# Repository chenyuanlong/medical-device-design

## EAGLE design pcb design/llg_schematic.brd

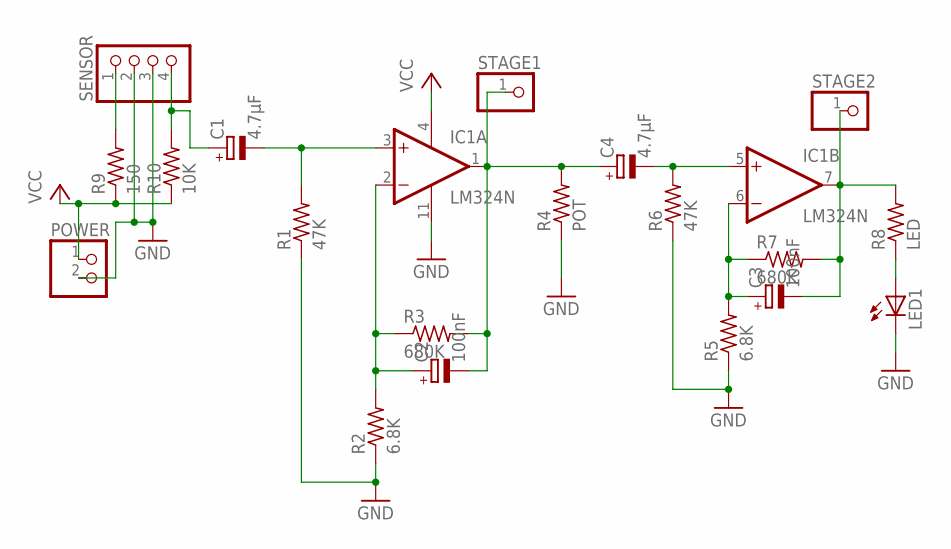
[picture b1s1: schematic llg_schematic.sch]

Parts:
C1, C4: 4.7μF; E2,5-6
C2, C3: 100nF; E2,5-6
IC1: LM324N; DIL14
LED1: LED5MM
POWER: PINHD-1X2; 1X02
R1, R6: 47K; 0204/7
R2, R5: 6.8K; 0204/7
R3, R7: 680K; 0204/7
R4: POT; 0204/7
R8: LED; 0204/7
R9: 150; 0204/7
R10: 10K; 0204/7
SENSOR: PINHD-1X4; 1X04
STAGE1, STAGE2: PINHD-1X1; 1X01

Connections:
GND: IC1.11 (V-), LED1.K (C), POWER.2, R1.1, R2.1, R4.1, R5.1, R6.1, SENSOR.2, SENSOR.3
unnamed: C1.-, IC1.3 (+IN), R1.2
unnamed: C2.+, IC1.2 (-IN), R2.2, R3.1
unnamed: C2.-, C4.+, IC1.1 (OUT), R3.2, R4.2, STAGE1.1
unnamed: C4.-, IC1.5 (+IN), R6.2
unnamed: C3.+, IC1.6 (-IN), R5.2, R7.1
unnamed: C3.-, IC1.7 (OUT), R7.2, R8.2, STAGE2.1
unnamed: R9.2, SENSOR.1
unnamed: LED1.A, R8.1
unnamed: C1.+, R10.2, SENSOR.4
VCC: IC1.4 (V+), POWER.1, R9.1, R10.1

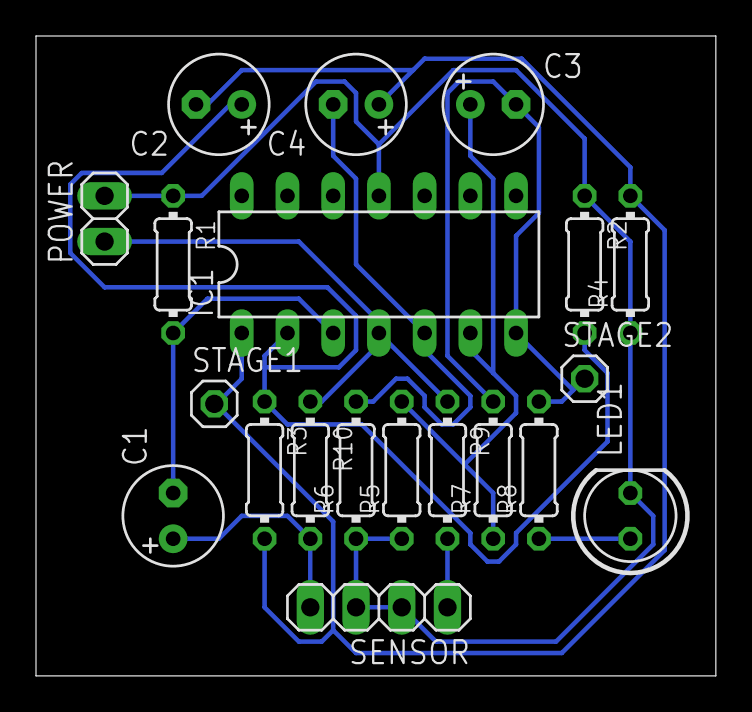
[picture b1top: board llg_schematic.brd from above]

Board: 2 copper layers, 37.8 x 35.5 mm, 20 parts (0 on the bottom side), 11 nets.

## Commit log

2017-09-06 created folder
2017-09-14 added python script
2017-09-18 added ble transmission
2017-09-23 fixed bluetooth transmission
2017-09-28 fixed double octet problem
2017-09-28 fixed for demo
2017-10-19 fixed bluefruit hex bug and improved sampling rate
2017-10-20 added OLED code
2017-10-24 added pcb schematics
2017-10-31 change transmission method to bleuart
2017-11-07 Added code for OLED display
2017-11-12 added storage and retrieval code
2017-11-14 fixed graph plotting and BLE transmission
2017-11-14 added timestamp in plot
